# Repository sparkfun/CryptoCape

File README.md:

CryptoCape
==========

[*CryptoCape (DEV-12773)*](https://www.sparkfun.com/products/12773)

A Cryptography Cape for the BeagleBone Black.

Repository Contents
-------------------

* **/Documentation** - PDF print of the board.
* **/Hardware** - All Eagle design files (.brd, .sch)
* **/Production** - Test bed files and production panel files

Documentation
--------------
* **[Hookup Guide](https://learn.sparkfun.com/tutorials/cryptocape-hookup-guide)** - Basic hookup guide for the CryptoCape.
* **[SparkFun Fritzing repo](https://github.com/sparkfun/Fritzing_Parts)** - Fritzing diagrams for SparkFun products.
* **[SparkFun 3D Model repo](https://github.com/sparkfun/3D_Models)** - 3D models of SparkFun products. 

License Information
-------------------

This product is _**open source**_! 

The hardware is released under [Creative Commons Share-alike 3.0](http://creativecommons.org/licenses/by-sa/3.0/).

If you have any questions or concerns on licensing, please contact techsupport@sparkfun.com.

Distributed as-is; no warranty is given.

- Your friends at SparkFun.

_This board is a collaboration with Josh Datko at Cryptotronix._

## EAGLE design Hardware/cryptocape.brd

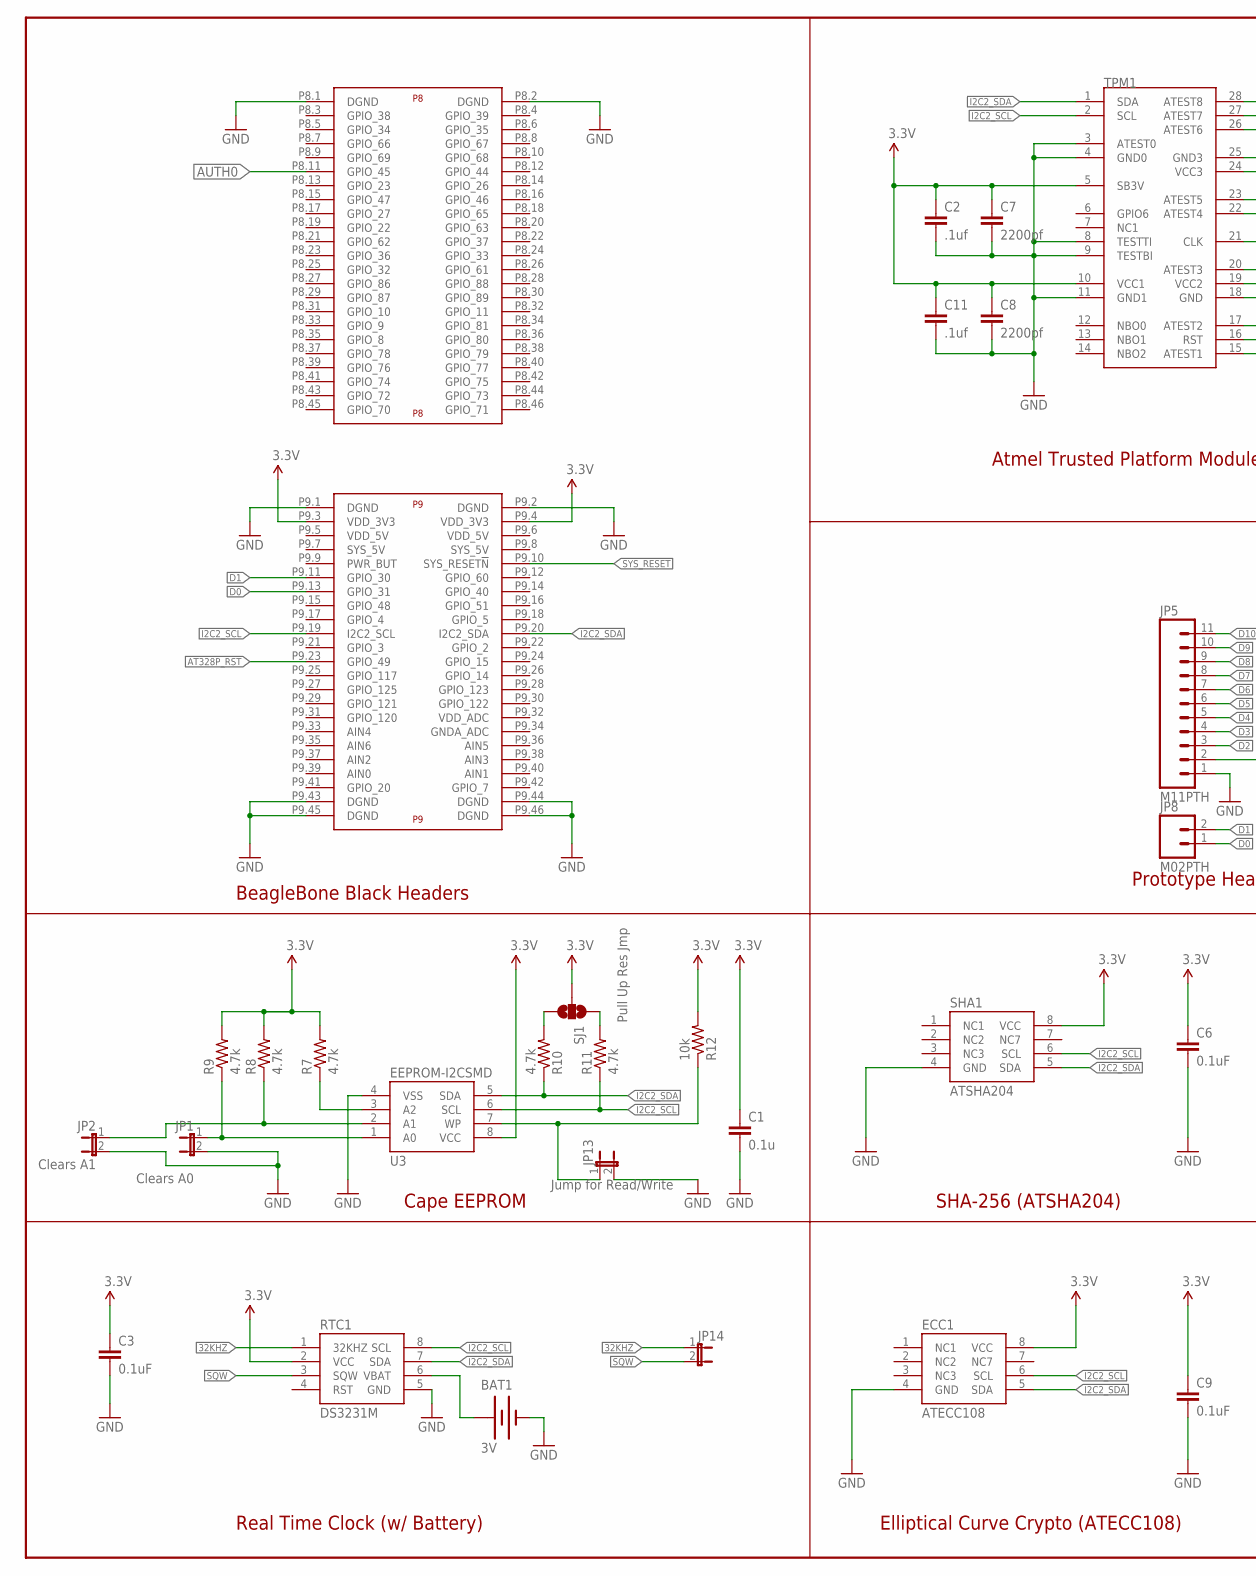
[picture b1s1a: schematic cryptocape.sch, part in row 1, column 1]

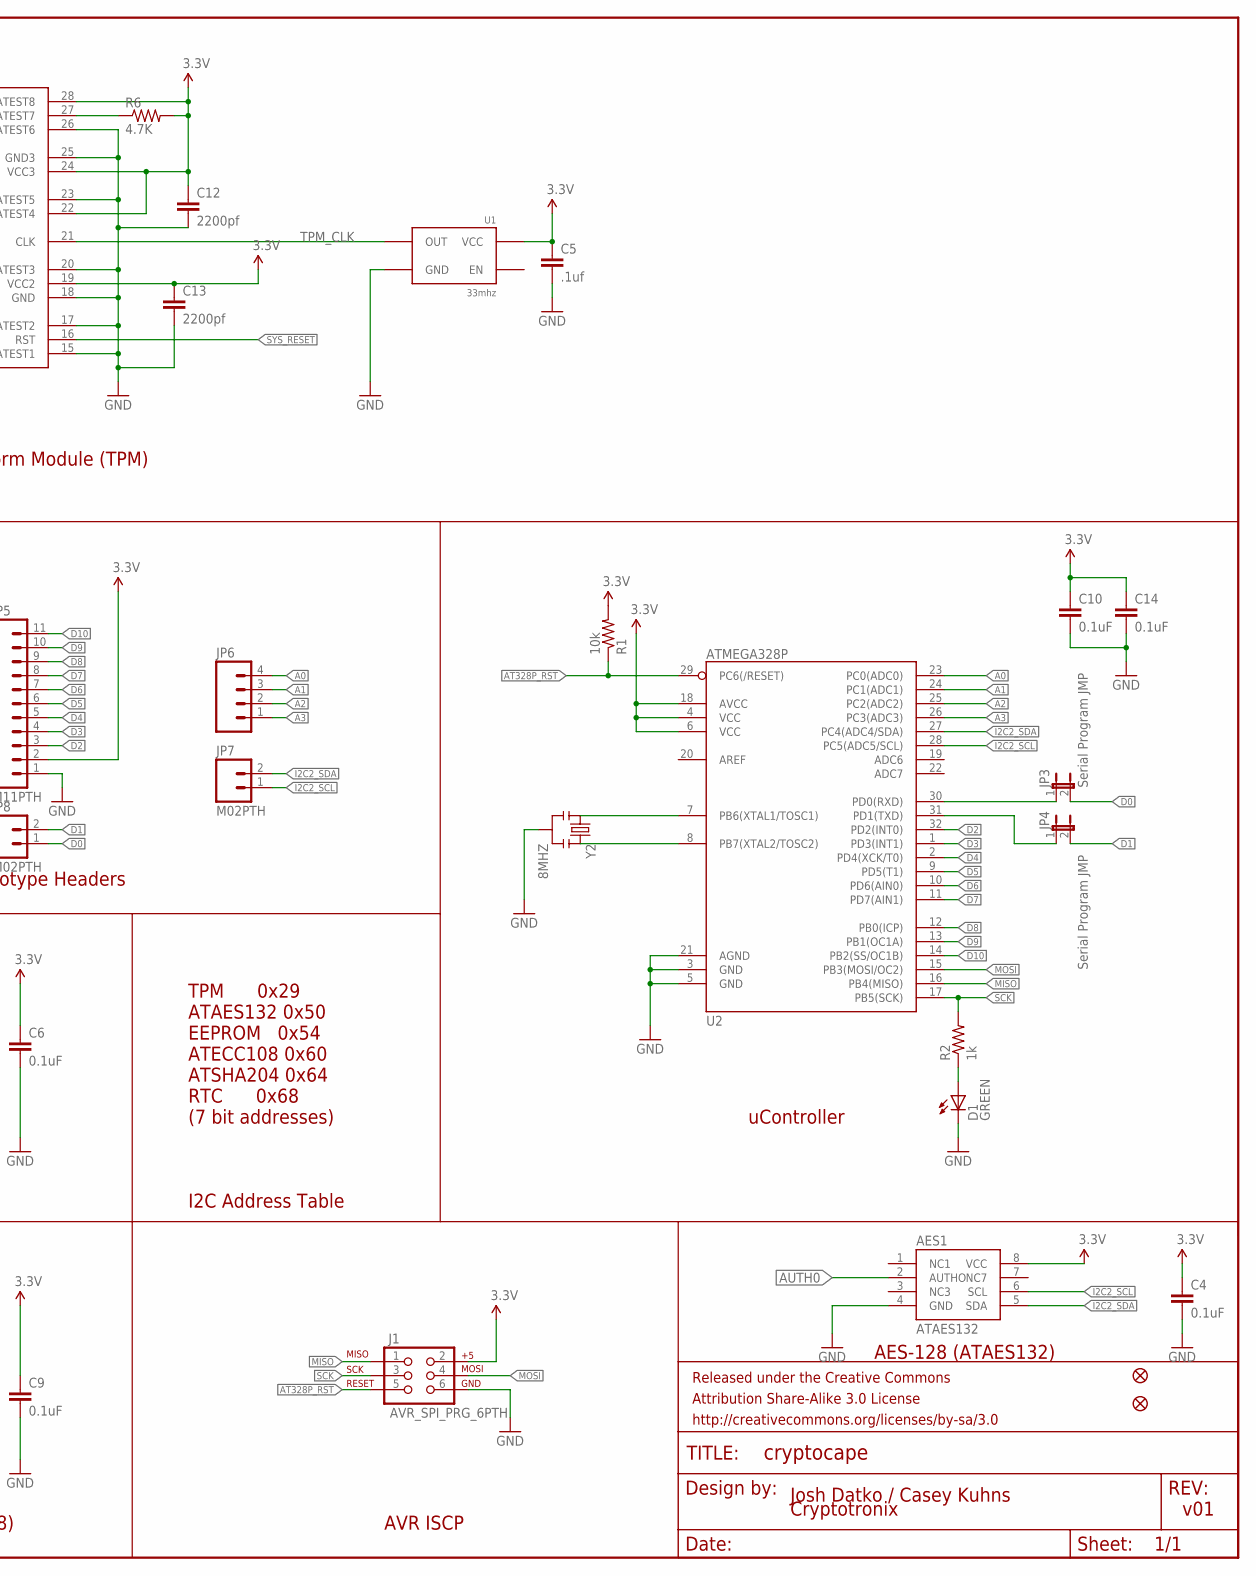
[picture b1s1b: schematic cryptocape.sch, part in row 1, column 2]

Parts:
AES1: ATAES132; SOIC8
BAT1: 3V; BATTCON_12MM
C1: 0.1u; 0603-CAP
C2, C5, C11: .1uf; 0603-CAP
C3, C4, C6, C9, C10, C14: 0.1uF; 0603-CAP
C7, C8, C12, C13: 2200pf; 0603-CAP
D1: GREEN; LED-0603
ECC1: ATECC108; SOIC8
FID1, FID2: FIDUCIAL1X2; FIDUCIAL-1X2
FRAME1: FRAME-LEDGER; CREATIVE_COMMONS
J1: AVR_SPI_PRG_6PTH; 2X3
JP1: Clears A0; SJ_2S-NO
JP2: Clears A1; SJ_2S-NO
JP3, JP4: Serial Program JMP; 1X02
JP5: M11PTH; 1X11
JP6: M04PTH; 1X04
JP7, JP8: M02PTH; 1X02
JP13: Jump for Read/Write; 1X02
JP14: JUMPER-2PTH; 1X02
R1, R12: 10k; 0603-RES
R2: 1k; 0603-RES
R6: 4.7K; 0603
R7, R8, R9, R10, R11: 4.7k; 0603
RTC1: DS3231M; SOIC8
SHA1: ATSHA204; SOIC8
SJ1: Pull Up Res Jmp; SJ_3_PASTE1&2&3
TPM1: AT97SC3204T; TSSOP28
U1: 33mhz; CRYSTAL-OSC-SMD-5X3.2
U2: ATMEGA328P; TQFP32-08
U3: EEPROM-I2CSMD; SO08
U$2: BEAGLE_BONE_BLACK_CAPE
Y2: 8MHZ; RESONATOR-SMD

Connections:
3.3V: AES1.8 (VCC), C1.1, C2.1, C3.1, C4.1, C5.1, C6.1, C7.1, C8.1, C9.1, C10.1, C11.1, C12.1, C13.1, C14.1, ECC1.8 (VCC), J1.2, JP5.2, R1.2, R6.2, R7.2, R8.2, R9.2, R12.2, RTC1.2 (VCC), SHA1.8 (VCC), SJ1.2, TPM1.5 (SB3V), TPM1.10 (VCC1), TPM1.19 (VCC2), TPM1.22 (ATEST4), TPM1.24 (VCC3), TPM1.28 (ATEST8), U1.4 (VCC), U2.4 (VCC), U2.6 (VCC), U2.18 (AVCC), U3.8 (VCC), U$2.P9.3 (VDD_3V3), U$2.P9.4 (VDD_3V3)
32KHZ: JP14.1, RTC1.1 (32KHZ)
A0: JP6.4, U2.23 (PC0(ADC0))
A1: JP6.3, U2.24 (PC1(ADC1))
A2: JP6.2, U2.25 (PC2(ADC2))
A3: JP6.1, U2.26 (PC3(ADC3))
AT328P_RST: J1.5, R1.1, U2.29 (PC6(/RESET)), U$2.P9.23 (GPIO_49)
AUTH0: AES1.2 (AUTHO), U$2.P8.11 (GPIO_45)
D0: JP3.2, JP8.1, U$2.P9.13 (GPIO_31)
D0': JP3.1, U2.30 (PD0(RXD))
D1: JP4.2, JP8.2, U$2.P9.11 (GPIO_30)
D1': JP4.1, U2.31 (PD1(TXD))
D2: JP5.3, U2.32 (PD2(INT0))
D3: JP5.4, U2.1 (PD3(INT1))
D4: JP5.5, U2.2 (PD4(XCK/T0))
D5: JP5.6, U2.9 (PD5(T1))
D6: JP5.7, U2.10 (PD6(AIN0))
D7: JP5.8, U2.11 (PD7(AIN1))
D8: JP5.9, U2.12 (PB0(ICP))
D9: JP5.10, U2.13 (PB1(OC1A))
D10: JP5.11, U2.14 (PB2(SS/OC1B))
GND: AES1.4 (GND), BAT1.GND (-), C1.2, C2.2, C3.2, C4.2, C5.2, C6.2, C7.2, C8.2, C9.2, C10.2, C11.2, C12.2, C13.2, C14.2, D1.C, ECC1.4 (GND), J1.6, JP1.2, JP2.2, JP5.1, JP13.2, RTC1.5 (GND), SHA1.4 (GND), TPM1.3 (ATEST0), TPM1.4 (GND0), TPM1.8 (TESTTI), TPM1.9 (TESTBI), TPM1.11 (GND1), TPM1.15 (ATEST1), TPM1.17 (ATEST2), TPM1.18 (GND), TPM1.20 (ATEST3), TPM1.23 (ATEST5), TPM1.25 (GND3), TPM1.26 (ATEST6), U1.2 (GND), U2.3 (GND), U2.5 (GND), U2.21 (AGND), U3.4 (VSS), U$2.P8.1 (DGND), U$2.P8.2 (DGND), U$2.P9.1 (DGND), U$2.P9.2 (DGND), U$2.P9.43 (DGND), U$2.P9.44 (DGND), U$2.P9.45 (DGND), U$2.P9.46 (DGND), Y2.2
I2C2_SCL: AES1.6 (SCL), ECC1.6 (SCL), JP7.1, R11.1, RTC1.8 (SCL), SHA1.6 (SCL), TPM1.2 (SCL), U2.28 (PC5(ADC5/SCL)), U3.6 (SCL), U$2.P9.19 (I2C2_SCL)
I2C2_SDA: AES1.5 (SDA), ECC1.5 (SDA), JP7.2, R10.1, RTC1.7 (SDA), SHA1.5 (SDA), TPM1.1 (SDA), U2.27 (PC4(ADC4/SDA)), U3.5 (SDA), U$2.P9.20 (I2C2_SDA)
MISO: J1.1, U2.16 (PB4(MISO))
MOSI: J1.4, U2.15 (PB3(MOSI/OC2))
unnamed: JP13.1, R12.1, U3.7 (WP)
unnamed: U2.7 (PB6(XTAL1/TOSC1)), Y2.1
unnamed: U2.8 (PB7(XTAL2/TOSC2)), Y2.3
unnamed: D1.A, R2.1
unnamed: R7.1, U3.3 (A2)
unnamed: R6.1, TPM1.27 (ATEST7)
unnamed: JP2.1, R8.1, U3.2 (A1)
unnamed: JP1.1, R9.1, U3.1 (A0)
unnamed: R10.2, SJ1.3
unnamed: R11.2, SJ1.1
SCK: J1.3, R2.2, U2.17 (PB5(SCK))
SQW: JP14.2, RTC1.3 (SQW)
SYS_RESET: TPM1.16 (RST), U$2.P9.10 (SYS_RESET!N)
TPM_CLK: TPM1.21 (CLK), U1.3 (OUT)
VBAT: BAT1.PWR@1 (+), RTC1.6 (VBAT)

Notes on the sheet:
Cryptotronix
BeagleBone Black Headers
Cape EEPROM
Real Time Clock (w/ Battery)
Atmel Trusted Platform Module (TPM)
Elliptical Curve Crypto (ATECC108)
AVR ISCP
uController
SHA-256 (ATSHA204)
Prototype Headers
I2C Address Table
TPM 0x29 ATAES132 0x50 EEPROM 0x54 ATECC108 0x60 ATSHA204 0x64 RTC 0x68 (7 bit addresses)
AES-128 (ATAES132)
Josh Datko / Casey Kuhns
v01

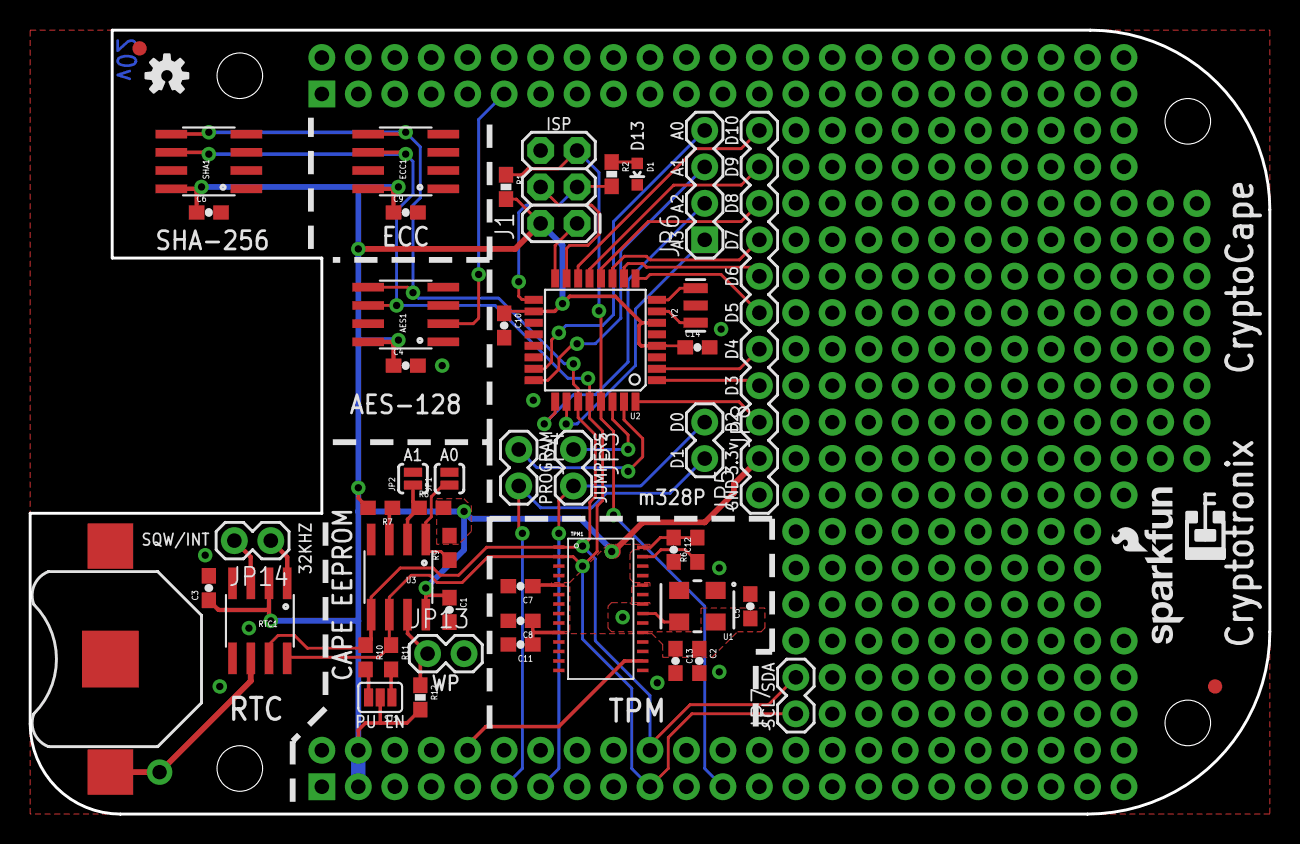
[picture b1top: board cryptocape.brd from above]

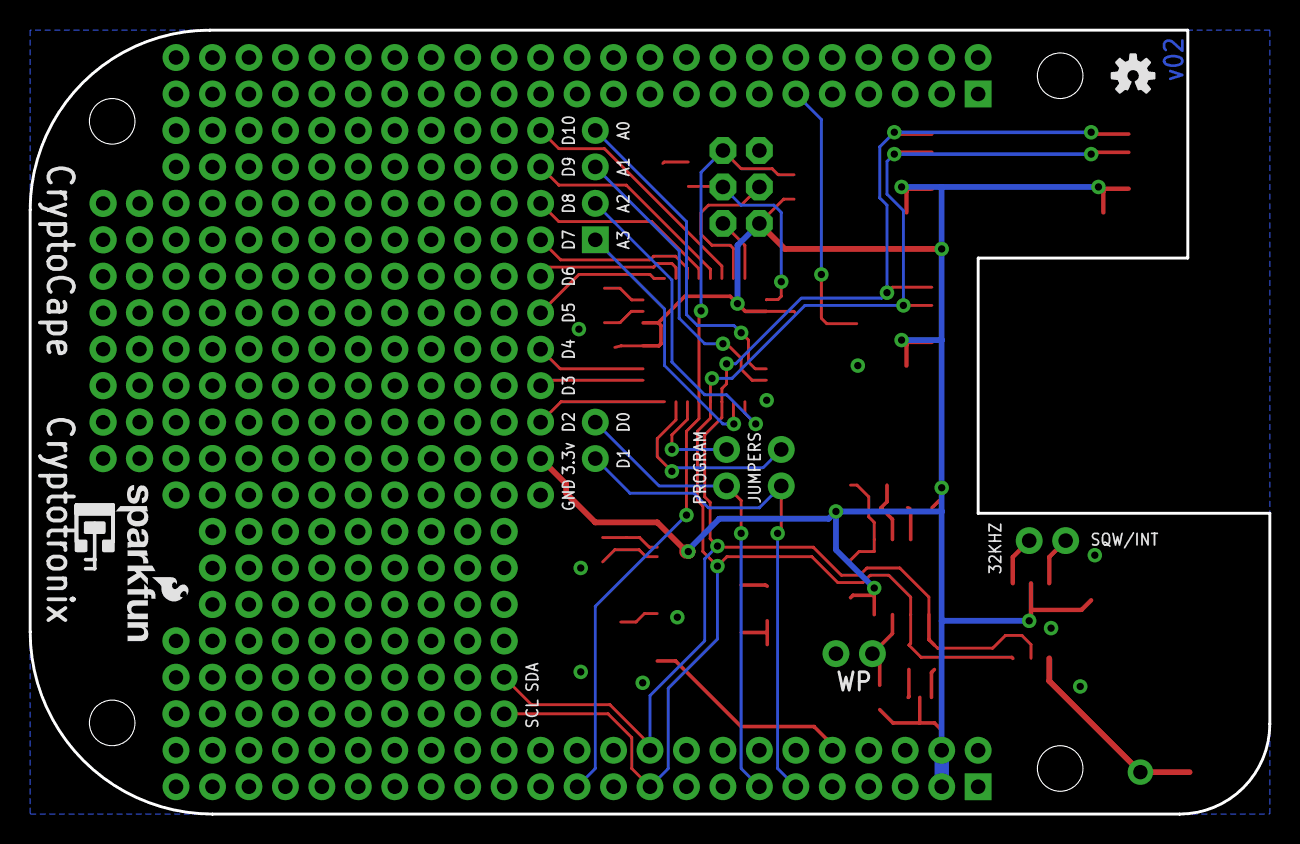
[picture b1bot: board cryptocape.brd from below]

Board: 2 copper layers, 86.4 x 54.6 mm, 54 parts (2 on the bottom side), 41 nets.

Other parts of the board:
U$3, U$6: OSHW-LOGO-S
U$4, U$5: SFE_LOGO_NAME_FLAME_.1

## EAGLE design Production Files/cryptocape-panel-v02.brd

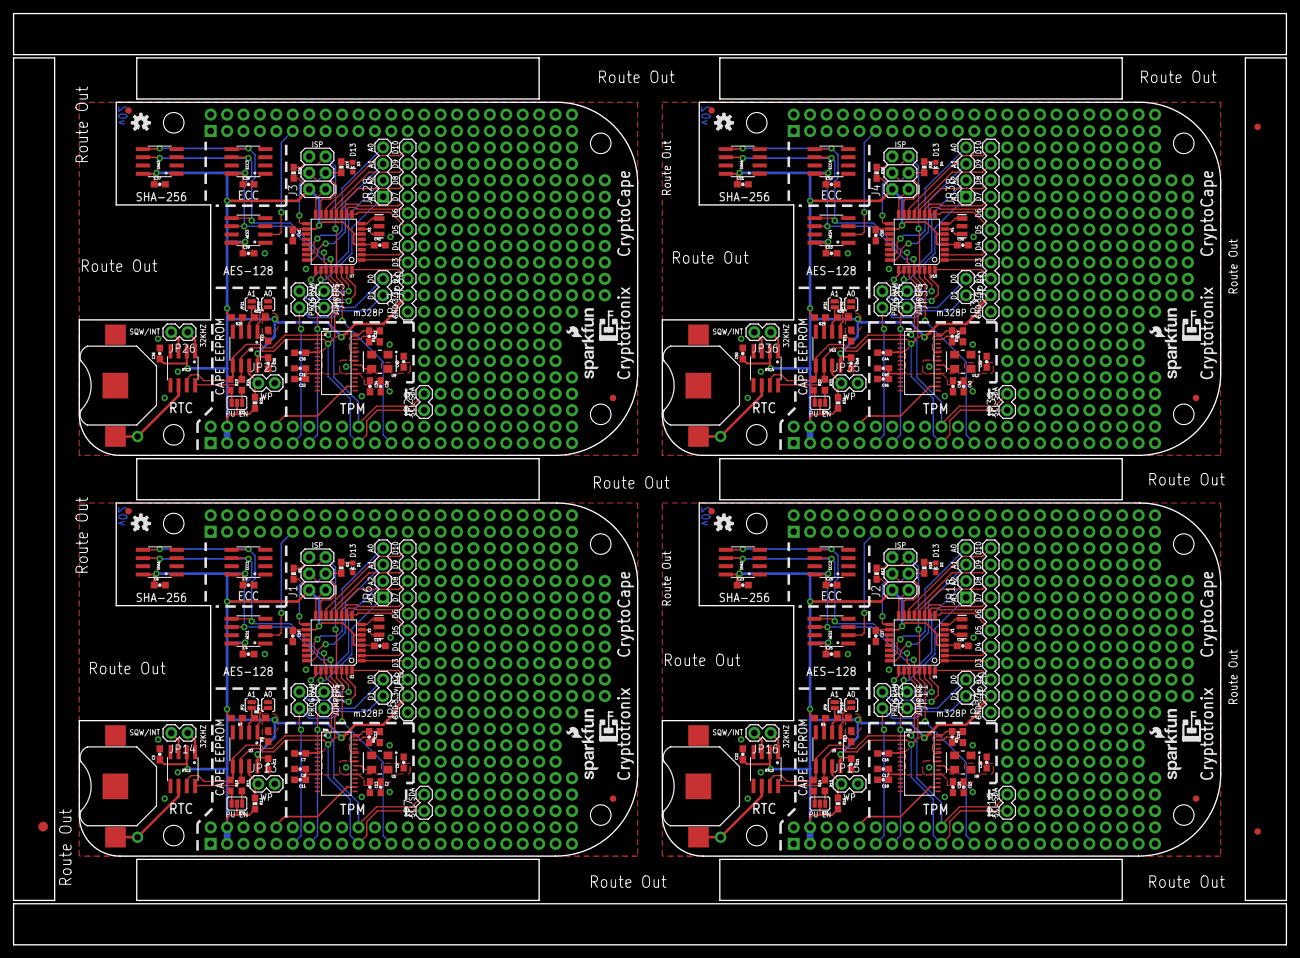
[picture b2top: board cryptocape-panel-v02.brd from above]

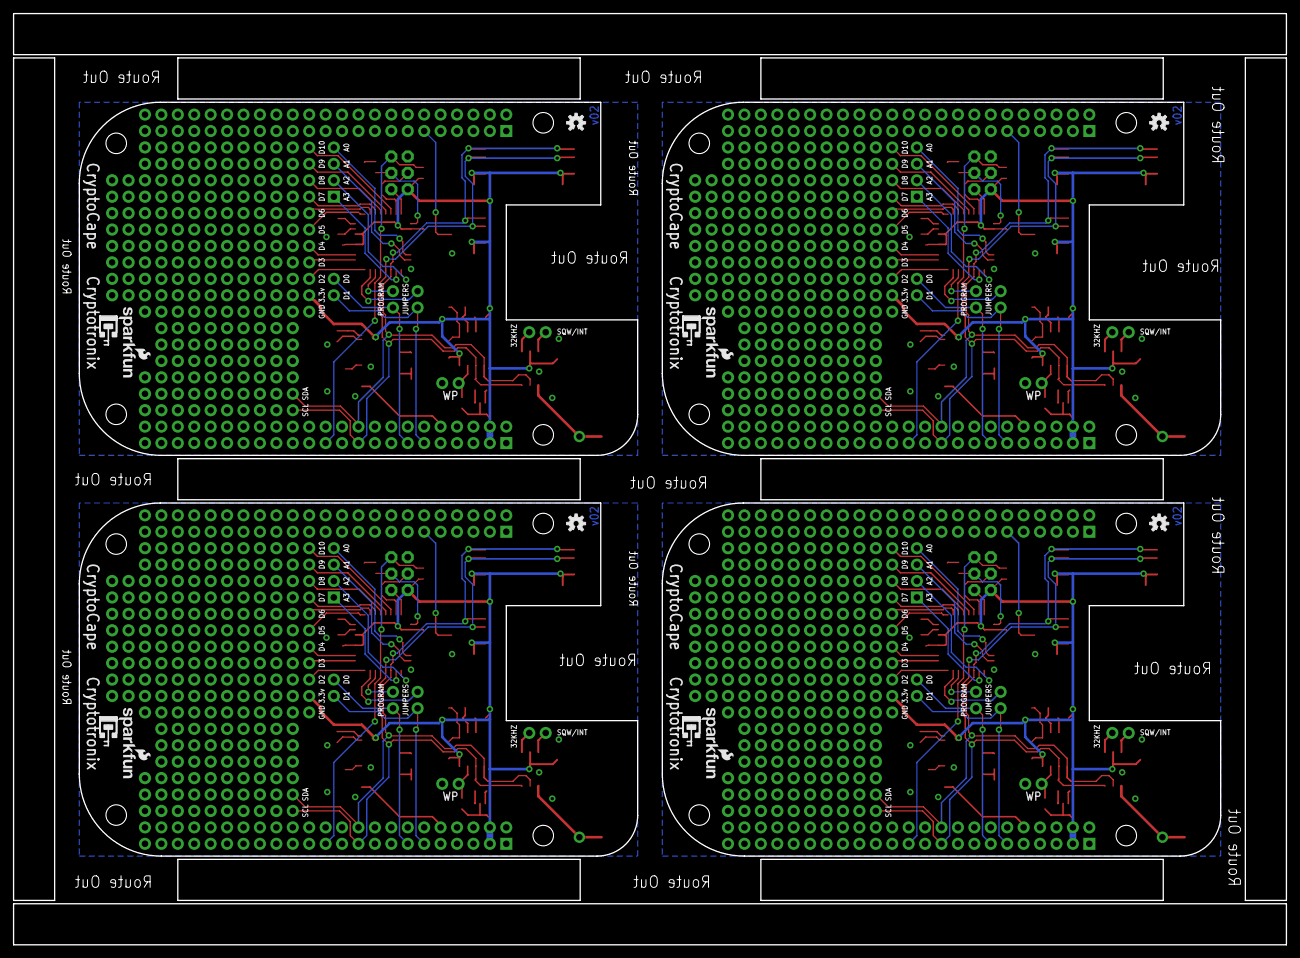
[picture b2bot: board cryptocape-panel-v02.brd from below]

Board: 2 copper layers, 196.8 x 144.0 mm, 215 parts (8 on the bottom side), 164 nets.

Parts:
AES1, AES2, AES3, AES4: ATAES132; SOIC8
BAT1, BAT2, BAT3, BAT4: 3V; BATTCON_12MM
C1, C21, C35, C49: 0.1u; 0603-CAP
C2, C5, C11, C15, C18, C26, C29, C32, C40, C43, C46, C54: .1uf; 0603-CAP
C3, C4, C6, C9, C10, C14, C22, C23, C24, C25, C27, C28, C36, C37, C38, C39, C41, C42, C50, C51, C52, C53, C55, C56: 0.1uF; 0603-CAP
C7, C8, C12, C13, C16, C17, C19, C20, C30, C31, C33, C34, C44, C45, C47, C48: 2200pf; 0603-CAP
D1, D2, D3, D4: GREEN; LED-0603
E$1: FIDUCIAL-1.5X3
E$12, E$14: FIDUCIAL-1X2
ECC1, ECC2, ECC3, ECC4: ATECC108; SOIC8
FID1, FID2, FID3, FID4, FID5, FID6, FID7, FID8: FIDUCIAL1X2; FIDUCIAL-1X2
J1, J2, J3, J4: AVR_SPI_PRG_6PTH; 2X3
JP1, JP10, JP22, JP32: Clears A0; SJ_2S-NO
JP2, JP9, JP21, JP31: Clears A1; SJ_2S-NO
JP3, JP4, JP11, JP12, JP23, JP24, JP33, JP34: Serial Program JMP; 1X02
JP5, JP17, JP27, JP37: M11PTH; 1X11
JP6, JP18, JP28, JP38: 1X04
JP7, JP8, JP19, JP20, JP29, JP30, JP39, JP40: M02PTH; 1X02
JP13, JP15, JP25, JP35: Jump for Read/Write; 1X02
JP14, JP16, JP26, JP36: 1X02
R1, R12, R16, R17, R25, R26, R34, R35: 10k; 0603-RES
R2, R18, R27, R36: 1k; 0603-RES
R3, R6, R19, R28: 4.7K; 0603
R4, R5, R7, R8, R9, R10, R11, R13, R14, R15, R20, R21, R22, R23, R24, R29, R30, R31, R32, R33: 4.7k; 0603
RTC1, RTC2, RTC3, RTC4: DS3231M; SOIC8
SHA1, SHA2, SHA3, SHA4: ATSHA204; SOIC8
SJ1, SJ2, SJ3, SJ4: Pull Up Res Jmp; SJ_3_PASTE1&2&3
TPM1, TPM2, TPM3, TPM4: AT97SC3204T; TSSOP28
U1, U6, U9, U12: 33mhz; CRYSTAL-OSC-SMD-5X3.2
U2, U4, U7, U10: ATMEGA328P; TQFP32-08
U3, U5, U8, U11: EEPROM-I2CSMD; SO08
U$1, U$2, U$11, U$16: BEAGLE_BONE_BLACK_CAPE
U$3, U$6, U$7, U$10, U$12, U$15, U$17, U$20: OSHW-LOGO-S
U$4, U$5, U$8, U$9, U$13, U$14, U$18, U$19: SFE_LOGO_NAME_FLAME_.1
Y1, Y2, Y3, Y4: 8MHZ; RESONATOR-SMD

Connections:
3.3V: AES1.8, C1.1, C2.1, C3.1, C4.1, C5.1, C6.1, C7.1, C8.1, C9.1, C10.1, C11.1, C12.1, C13.1, C14.1, ECC1.8, J1.2, JP5.2, R1.2, R6.2, R7.2, R8.2, R9.2, R12.2, RTC1.2, SHA1.8, SJ1.2, TPM1.5, TPM1.10, TPM1.19, TPM1.22, TPM1.24, TPM1.28, U1.4, U2.4, U2.6, U2.18, U3.8, U$2.P9.3, U$2.P9.4
3.3V1: AES2.8, C15.1, C16.1, C17.1, C18.1, C19.1, C20.1, C21.1, C22.1, C23.1, C24.1, C25.1, C26.1, C27.1, C28.1, ECC2.8, J2.2, JP17.2, R3.2, R4.2, R5.2, R13.2, R16.2, R17.2, RTC2.2, SHA2.8, SJ2.2, TPM2.5, TPM2.10, TPM2.19, TPM2.22, TPM2.24, TPM2.28, U4.4, U4.6, U4.18, U5.8, U6.4, U$1.P9.3, U$1.P9.4
3.3V2: AES3.8, C29.1, C30.1, C31.1, C32.1, C33.1, C34.1, C35.1, C36.1, C37.1, C38.1, C39.1, C40.1, C41.1, C42.1, ECC3.8, J3.2, JP27.2, R19.2, R20.2, R21.2, R22.2, R25.2, R26.2, RTC3.2, SHA3.8, SJ3.2, TPM3.5, TPM3.10, TPM3.19, TPM3.22, TPM3.24, TPM3.28, U7.4, U7.6, U7.18, U8.8, U9.4, U$11.P9.3, U$11.P9.4
3.3V3: AES4.8, C43.1, C44.1, C45.1, C46.1, C47.1, C48.1, C49.1, C50.1, C51.1, C52.1, C53.1, C54.1, C55.1, C56.1, ECC4.8, J4.2, JP37.2, R28.2, R29.2, R30.2, R31.2, R34.2, R35.2, RTC4.2, SHA4.8, SJ4.2, TPM4.5, TPM4.10, TPM4.19, TPM4.22, TPM4.24, TPM4.28, U10.4, U10.6, U10.18, U11.8, U12.4, U$16.P9.3, U$16.P9.4
32KHZ: JP14.1, RTC1.1
32KHZ1: JP16.1, RTC2.1
32KHZ2: JP26.1, RTC3.1
32KHZ3: JP36.1, RTC4.1
A0: JP6.4, U2.23
A1: JP6.3, U2.24
A2: JP6.2, U2.25
A3: JP6.1, U2.26
A4: JP18.3, U4.24
A5: JP18.2, U4.25
A6: JP18.1, U4.26
A7: JP18.4, U4.23
A8: JP28.3, U7.24
A9: JP28.2, U7.25
A10: JP28.1, U7.26
A11: JP28.4, U7.23
A12: JP38.3, U10.24
A13: JP38.2, U10.25
A14: JP38.1, U10.26
A15: JP38.4, U10.23
AT328P_RST: J1.5, R1.1, U2.29, U$2.P9.23
AT328P_RST1: J2.5, R17.1, U4.29, U$1.P9.23
AT328P_RST2: J3.5, R26.1, U7.29, U$11.P9.23
AT328P_RST3: J4.5, R35.1, U10.29, U$16.P9.23
AUTH0: AES1.2, U$2.P8.11
AUTH1: AES2.2, U$1.P8.11
AUTH2: AES3.2, U$11.P8.11
AUTH3: AES4.2, U$16.P8.11
D0: JP3.2, JP8.1, U$2.P9.13
D0': JP3.1, U2.30
D0'1: JP11.1, U4.30
D0'2: JP23.1, U7.30
D0'3: JP33.1, U10.30
D1: JP4.2, JP8.2, U$2.P9.11
D1': JP4.1, U2.31
D1'1: JP12.1, U4.31
D1'2: JP24.1, U7.31
D1'3: JP34.1, U10.31
D2: JP5.3, U2.32
D3: JP5.4, U2.1
D4: JP5.5, U2.2
D5: JP5.6, U2.9
D6: JP5.7, U2.10
D7: JP5.8, U2.11
D8: JP5.9, U2.12
D9: JP5.10, U2.13
D10: JP5.11, U2.14
D11: JP11.2, JP20.1, U$1.P9.13
D12: JP12.2, JP20.2, U$1.P9.11
D13: JP17.3, U4.32
D14: JP17.4, U4.1
D15: JP17.5, U4.2
D16: JP17.6, U4.9
D17: JP17.7, U4.10
D18: JP17.8, U4.11
D19: JP17.9, U4.12
D20: JP17.10, U4.13
D21: JP17.11, U4.14
D22: JP23.2, JP30.1, U$11.P9.13
D23: JP24.2, JP30.2, U$11.P9.11
D24: JP27.3, U7.32
D25: JP27.4, U7.1
D26: JP27.5, U7.2
D27: JP27.6, U7.9
D28: JP27.7, U7.10
D29: JP27.8, U7.11
D30: JP27.9, U7.12
D31: JP27.10, U7.13
D32: JP27.11, U7.14
D33: JP33.2, JP40.1, U$16.P9.13
D34: JP34.2, JP40.2, U$16.P9.11
D35: JP37.3, U10.32
D36: JP37.4, U10.1
D37: JP37.5, U10.2
D38: JP37.6, U10.9
D39: JP37.7, U10.10
D40: JP37.8, U10.11
D41: JP37.9, U10.12
D42: JP37.10, U10.13
D43: JP37.11, U10.14
GND: AES1.4, BAT1.GND, C1.2, C2.2, C3.2, C4.2, C5.2, C6.2, C7.2, C8.2, C9.2, C10.2, C11.2, C12.2, C13.2, C14.2, D1.C, ECC1.4, J1.6, JP1.2, JP2.2, JP5.1, JP13.2, RTC1.5, SHA1.4, TPM1.3, TPM1.4, TPM1.8, TPM1.9, TPM1.11, TPM1.15, TPM1.17, TPM1.18, TPM1.20, TPM1.23, TPM1.25, TPM1.26, U1.2, U2.3, U2.5, U2.21, U3.4, U$2.P8.1, U$2.P8.2, U$2.P9.1, U$2.P9.2, U$2.P9.43, U$2.P9.44, U$2.P9.45, U$2.P9.46, Y2.2
GND1: AES2.4, BAT2.GND, C15.2, C16.2, C17.2, C18.2, C19.2, C20.2, C21.2, C22.2, C23.2, C24.2, C25.2, C26.2, C27.2, C28.2, D2.C, ECC2.4, J2.6, JP9.2, JP10.2, JP15.2, JP17.1, RTC2.5, SHA2.4, TPM2.3, TPM2.4, TPM2.8, TPM2.9, TPM2.11, TPM2.15, TPM2.17, TPM2.18, TPM2.20, TPM2.23, TPM2.25, TPM2.26, U4.3, U4.5, U4.21, U5.4, U6.2, U$1.P8.1, U$1.P8.2, U$1.P9.1, U$1.P9.2, U$1.P9.43, U$1.P9.44, U$1.P9.45, U$1.P9.46, Y1.2
GND2: AES3.4, BAT3.GND, C29.2, C30.2, C31.2, C32.2, C33.2, C34.2, C35.2, C36.2, C37.2, C38.2, C39.2, C40.2, C41.2, C42.2, D3.C, ECC3.4, J3.6, JP21.2, JP22.2, JP25.2, JP27.1, RTC3.5, SHA3.4, TPM3.3, TPM3.4, TPM3.8, TPM3.9, TPM3.11, TPM3.15, TPM3.17, TPM3.18, TPM3.20, TPM3.23, TPM3.25, TPM3.26, U7.3, U7.5, U7.21, U8.4, U9.2, U$11.P8.1, U$11.P8.2, U$11.P9.1, U$11.P9.2, U$11.P9.43, U$11.P9.44, U$11.P9.45, U$11.P9.46, Y3.2
GND3: AES4.4, BAT4.GND, C43.2, C44.2, C45.2, C46.2, C47.2, C48.2, C49.2, C50.2, C51.2, C52.2, C53.2, C54.2, C55.2, C56.2, D4.C, ECC4.4, J4.6, JP31.2, JP32.2, JP35.2, JP37.1, RTC4.5, SHA4.4, TPM4.3, TPM4.4, TPM4.8, TPM4.9, TPM4.11, TPM4.15, TPM4.17, TPM4.18, TPM4.20, TPM4.23, TPM4.25, TPM4.26, U10.3, U10.5, U10.21, U11.4, U12.2, U$16.P8.1, U$16.P8.2, U$16.P9.1, U$16.P9.2, U$16.P9.43, U$16.P9.44, U$16.P9.45, U$16.P9.46, Y4.2
I2C2_SCL: AES1.6, ECC1.6, JP7.1, R11.1, RTC1.8, SHA1.6, TPM1.2, U2.28, U3.6, U$2.P9.19
I2C2_SCL1: AES2.6, ECC2.6, JP19.1, R15.1, RTC2.8, SHA2.6, TPM2.2, U4.28, U5.6, U$1.P9.19
I2C2_SCL2: AES3.6, ECC3.6, JP29.1, R24.1, RTC3.8, SHA3.6, TPM3.2, U7.28, U8.6, U$11.P9.19
I2C2_SCL3: AES4.6, ECC4.6, JP39.1, R33.1, RTC4.8, SHA4.6, TPM4.2, U10.28, U11.6, U$16.P9.19
I2C2_SDA: AES1.5, ECC1.5, JP7.2, R10.1, RTC1.7, SHA1.5, TPM1.1, U2.27, U3.5, U$2.P9.20
I2C2_SDA1: AES2.5, ECC2.5, JP19.2, R14.1, RTC2.7, SHA2.5, TPM2.1, U4.27, U5.5, U$1.P9.20
I2C2_SDA2: AES3.5, ECC3.5, JP29.2, R23.1, RTC3.7, SHA3.5, TPM3.1, U7.27, U8.5, U$11.P9.20
I2C2_SDA3: AES4.5, ECC4.5, JP39.2, R32.1, RTC4.7, SHA4.5, TPM4.1, U10.27, U11.5, U$16.P9.20
MISO: J1.1, U2.16
MISO1: J2.1, U4.16
MISO2: J3.1, U7.16
MISO3: J4.1, U10.16
MOSI: J1.4, U2.15
MOSI1: J2.4, U4.15
MOSI2: J3.4, U7.15
MOSI3: J4.4, U10.15
unnamed: JP13.1, R12.1, U3.7
unnamed: U2.7, Y2.1
unnamed: U2.8, Y2.3
unnamed: D1.A, R2.1
unnamed: R7.1, U3.3
unnamed: R6.1, TPM1.27
unnamed: JP2.1, R8.1, U3.2
unnamed: JP1.1, R9.1, U3.1
unnamed: R10.2, SJ1.3
unnamed: R11.2, SJ1.1
unnamed: U4.7, Y1.1
unnamed: U4.8, Y1.3
unnamed: R3.1, TPM2.27
unnamed: R4.1, U5.3
unnamed: JP9.1, R5.1, U5.2
unnamed: JP10.1, R13.1, U5.1
unnamed: R14.2, SJ2.3
unnamed: R15.2, SJ2.1
unnamed: JP15.1, R16.1, U5.7
unnamed: D2.A, R18.1
unnamed: U7.7, Y3.1
unnamed: U7.8, Y3.3
unnamed: R19.1, TPM3.27
unnamed: R20.1, U8.3
unnamed: JP21.1, R21.1, U8.2
unnamed: JP22.1, R22.1, U8.1
unnamed: R23.2, SJ3.3
unnamed: R24.2, SJ3.1
unnamed: JP25.1, R25.1, U8.7
unnamed: D3.A, R27.1
unnamed: U10.7, Y4.1
unnamed: U10.8, Y4.3
unnamed: R28.1, TPM4.27
unnamed: R29.1, U11.3
unnamed: JP31.1, R30.1, U11.2
unnamed: JP32.1, R31.1, U11.1
unnamed: R32.2, SJ4.3
unnamed: R33.2, SJ4.1
unnamed: JP35.1, R34.1, U11.7
unnamed: D4.A, R36.1
SCK: J1.3, R2.2, U2.17
SCK1: J2.3, R18.2, U4.17
SCK2: J3.3, R27.2, U7.17
SCK3: J4.3, R36.2, U10.17
SQW: JP14.2, RTC1.3
SQW1: JP16.2, RTC2.3
SQW2: JP26.2, RTC3.3
SQW3: JP36.2, RTC4.3
SYS_RESET: TPM1.16, U$2.P9.10
SYS_RESET1: TPM2.16, U$1.P9.10
SYS_RESET2: TPM3.16, U$11.P9.10
SYS_RESET3: TPM4.16, U$16.P9.10
TPM_CLK: TPM1.21, U1.3
TPM_CLK1: TPM2.21, U6.3
TPM_CLK2: TPM3.21, U9.3
TPM_CLK3: TPM4.21, U12.3
VBAT: BAT1.PWR@1, RTC1.6
VBAT1: BAT2.PWR@1, RTC2.6
VBAT2: BAT3.PWR@1, RTC3.6
VBAT3: BAT4.PWR@1, RTC4.6

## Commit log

2014-01-17 Initial file commit
2014-01-18 Removes space between Crypto and Cape. Test commit.
2014-01-27 Fixes spacing and silk for jumpers
2014-01-30 tightening up footprints, still a work in progress
2014-01-31 Adds ATAES123 and Cryptotronix Logo
2014-02-04 finished layout with lables. Board is in state for review
2014-02-04 Fixed airwire issue
2014-02-04 Added label for I2C EN.
2014-02-04 added authors and version
2014-02-04 added authors on Schematic
2014-02-04 added version on schematic
2014-02-04 added v02
2014-02-04 fixed capacitor C7 alignment to match C11
2014-02-27 Fixed off angle wire and added TP for RTC battery.
2014-03-03 Superficial changes to schematic and board.
    - Fixes bent wire on schematic on BBB header.
    - Changes "set" to "clear" on EEPROM
    - Adds ATATES132 to I2C address list
    - Resorts the list by address
    - Changes "Atmel Trusted Platform Module" to TPM on brd
    - Changes "MEGA328" to "m328P"
2014-03-03 Code will be under various licenses, none of which is the beerware license.
2014-03-03 bumped some vias to clear DRC ready for RED
2014-03-04 Changed I2C EN to PU EN
2014-03-04 added fiducials
    regular local fiducials
2014-03-04 created panel v02
2014-03-04 added "route out" for PCB fab house
2014-03-25 fixed gitignore
2014-04-02 Initial Version of cape EEPROM. UNTESTED.
2014-04-03 Binary file now matches DTS file
2014-04-11 Adds example code to burn the EEPROM from the ATmega328p
2014-05-29 Adding product links to README
2014-05-29 Update README.md
    Deleting repo contents listed that do not exist
2015-12-09 Adding docoumentation with board pdf, updating readme, fixing directory name

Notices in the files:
parts and their libraries:
SparkFun-DigitalIC: Licensing: CC v3.0 Share-Alike You are welcome to use this library for commercial purposes.
SparkFun-Aesthetics: Released under the Creative Commons Attribution Share-Alike 3.0 License
SparkFun-Aesthetics: Released under the Creative Commons
